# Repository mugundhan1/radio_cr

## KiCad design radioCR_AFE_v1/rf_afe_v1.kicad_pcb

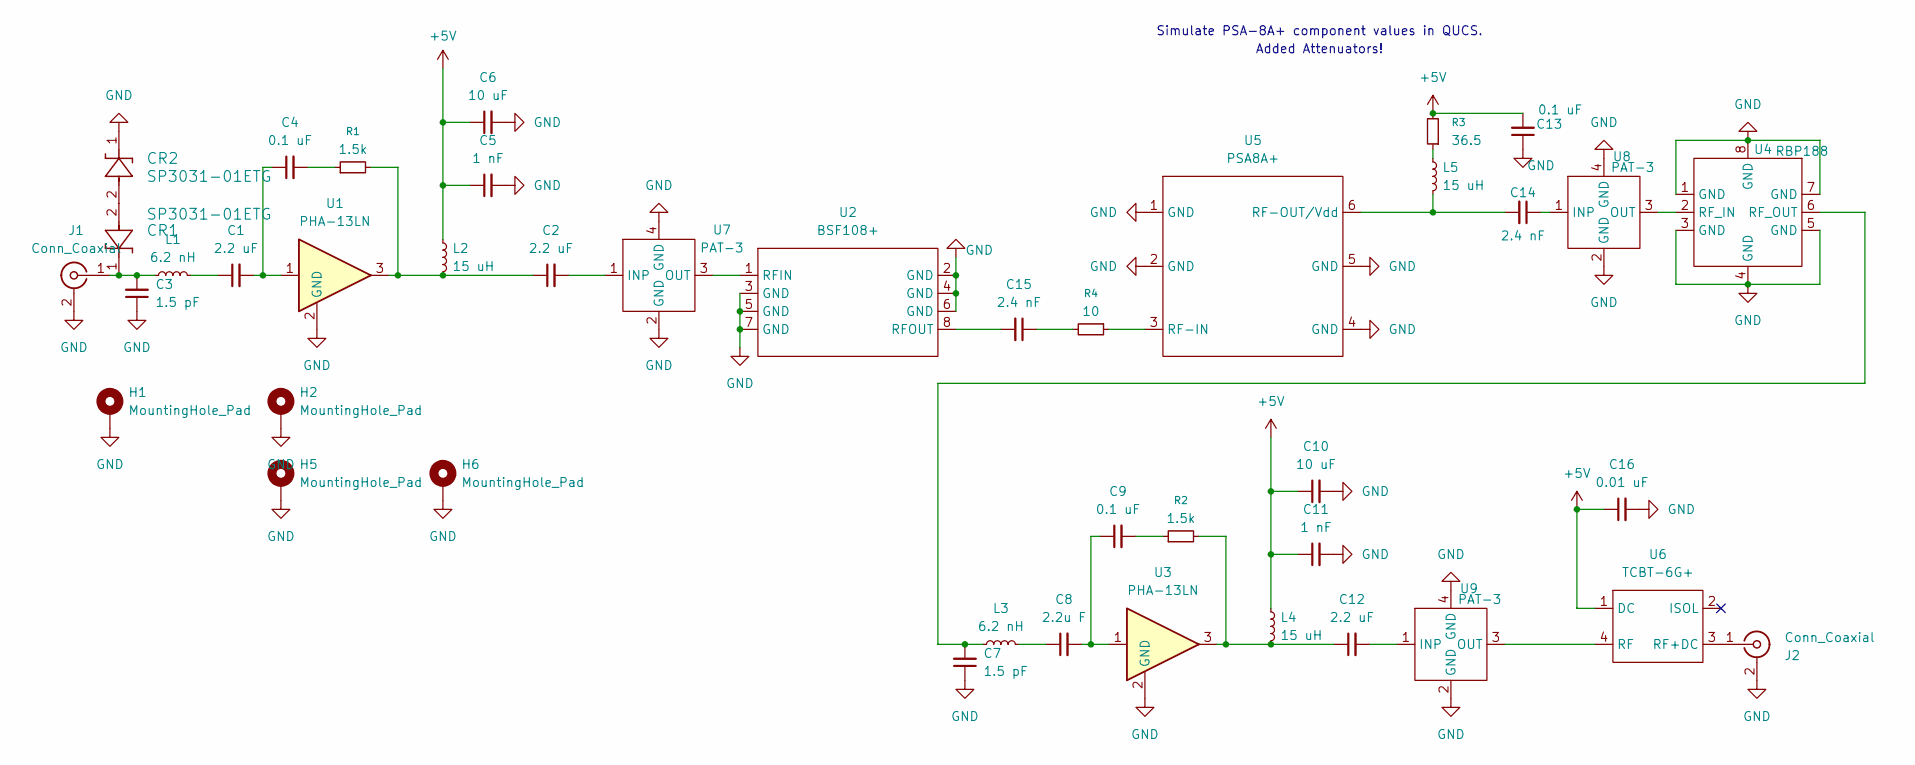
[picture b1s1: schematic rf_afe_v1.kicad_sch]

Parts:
C1, C2, C12: 2.2 uF; C_0805_2012Metric
C3, C7: 1.5 pF; C_0805_2012Metric
C4, C9, C13: 0.1 uF; C_0603_1608Metric
C5, C11: 1 nF; C_0603_1608Metric
C6, C10: 10 uF; C_0805_2012Metric
C8: 2.2u F; C_0805_2012Metric
C14, C15: 2.4 nF; C_0805_2012Metric
C16: 0.01 uF; C_0603_1608Metric
CR1, CR2: SP3031-01ETG; SOD882_LTF
H1, H2, H5, H6: MountingHole_Pad; MountingHole_2.7mm_M2.5_Pad_Via
J1, J2: Conn_Coaxial; SMA_Amphenol_132289_EdgeMount
L1, L3: 6.2 nH; L_0805_2012Metric
L2, L4, L5: 15 uH; L_1210_3225Metric
R1, R2: 1.5k; R_0805_2012Metric
R3: 36.5; R_0805_2012Metric
R4: 10; R_0805_2012Metric
U1, U3: PHA-13LN; SOT-89-3
U2: BSF108+; Mini-Circuits_HF1139_LandPatternPL-230
U4: RBP188; Mini-Circuits_GP731_LandPatternPL-176
U5: PSA8A+; SOT-363_SC-70-6_Handsoldering
U6: TCBT-6G+; GU1604
U7, U8, U9: PAT-3; PAT-3+

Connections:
+5V: C5.1, C6.1, C10.1, C11.1, C13.2, C16.1, L2.1, L4.1, R3.2, U6.1 (DC)
GND: C3.1, C5.2, C6.2, C7.1, C10.2, C11.2, C13.1, C16.2, CR2.1, H1.1, H2.1, H5.1, H6.1, J1.2 (Ext), J2.2 (Ext), U1.2 (GND), U2.2 (GND), U2.3 (GND), U2.4 (GND), U2.5 (GND), U2.6 (GND), U2.7 (GND), U3.2 (GND), U4.1 (GND), U4.3 (GND), U4.4 (GND), U4.5 (GND), U4.7 (GND), U4.8 (GND), U5.1 (GND), U5.2 (GND), U5.4 (GND), U5.5 (GND), U7.2 (GND), U7.4 (GND), U8.2 (GND), U8.4 (GND), U9.2 (GND), U9.4 (GND)
unnamed: C1.1, L1.2
unnamed: C1.2, C4.1, U1.1
unnamed: C2.1, L2.2, R1.2, U1.3
unnamed: C4.2, R1.1
unnamed: C8.1, L3.2
unnamed: C8.2, C9.1, U3.1
unnamed: C9.2, R2.1
unnamed: C12.1, L4.2, R2.2, U3.3
unnamed: C15.1, R4.2
unnamed: CR1.2, CR2.2
unnamed: C3.2, CR1.1, J1.1 (In), L1.1
unnamed: J2.1 (In), U6.3 (RF+DC)
unnamed: L5.1, R3.1
unnamed: U2.1 (RFIN), U7.3 (OUT)
unnamed: C15.2, U2.8 (RFOUT)
unnamed: U4.2 (RF_IN), U8.3 (OUT)
unnamed: C7.2, L3.1, U4.6 (RF_OUT)
unnamed: R4.1, U5.3 (RF-IN)
unnamed: C14.2, L5.2, U5.6 (RF-OUT/Vdd)
unnamed: U6.4 (RF), U9.3 (OUT)
unnamed: C2.2, U7.1 (INP)
unnamed: C14.1, U8.1 (INP)
unnamed: C12.2, U9.1 (INP)

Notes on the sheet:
Added Attenuators!
Simulate PSA-8A+ component values in QUCS.

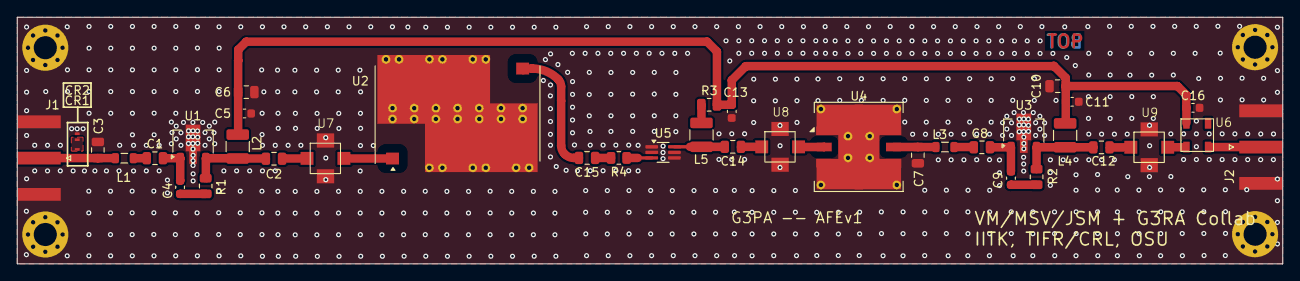
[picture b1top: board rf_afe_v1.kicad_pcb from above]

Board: 2 copper layers, 148.2 x 28.9 mm, 42 parts (0 on the bottom side), 25 nets.

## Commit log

2025-10-08 added cides
2025-11-13 add rfi data
2025-11-16 added folder for afe
2025-11-16 add respective folders
2025-11-18 added csv files
2025-12-04 code v1
2025-12-12 must add scint positions
2025-12-26 added lat long from google!
2026-01-17 added sch/pcb for afe (msv/vm)
2026-02-18 Redone according to new line-up as per matlab sims. Mask removed from board edge too!
2026-02-18 modified according to line-up results from Matlab, removed board edge mask
2026-02-19 removed missed out solder mask.
2026-02-19 Remove commented API key assignment
    Removed commented line for setting the STATIC_MAP_API_KEY.
2026-03-30 added component values
2026-03-30 added values
2026-04-02 attenuator added to schematic and PCB
2026-04-07 PCB fine tuned
    All errors removed
2026-04-19 updated C1 footprint, regen bom
2026-04-20 fixed some drc
